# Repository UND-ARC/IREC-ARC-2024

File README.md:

# IREC-Launch-Vehicle-2024
UND ARC Launch Vehicle for Spaceport America Cup 2024 

### Hardware
Link to Hardware List [WIP]
### Software
- Solidworks Student Edition 2022
- OpenRocket
- GIT
- GIT LFS (Large File Support)
- GitHub Desktop
## Getting Started
### Installing and Setting Up the Repository
1) Create a GitHub Account
2) Download and install Git [LINK](https://git-scm.com/downloads)
3) Download and install Git LFS [LINK](https://git-lfs.github.com/)
4) Download and install GitHub Desktop [LINK](https://desktop.github.com/)
5) Sign into GitHub Desktop with GitHub Account
6) Create a local copy of the Repository opeing 'File -> Clone repository -> URL'
7) Enter: [https://github.com/UND-ARC/RocketModels-2023.git](https://github.com/UND-ARC/RocketModels-2023.git)
8) Set your local path to 'C:/Projects/RocketModels-2023'. Note, you may need to create manually the Projects folder (do not create the 'RocketModels-2023' folder)
9) Open file explorer and navigate to 'C:/Projects/RocketModels-2023'
10) Right click in the folder and select 'Git Bash Here'
11) Enter the command `git lfs install`. This will enable the large file support.
12) Message Neko'z in discord to get added to the members list for write access
### When editing files
Since files are stored as binary (unreadable to humans) it is important that no two file have a merge conflict. This can be done by "locking" a file when we edit it which prevents others from making changes to it at the same time.

To Lock a file, right click in the folder the file is in and select "Git bash here". Then enter the command:
`git lfs lock FILENAME.Ext`
To Unlock a file use the command:
`git lfs unlock FILENAME.Ext`
The command `ls` will list all the files in the current folder if you don't know the extension. To see all the files that are currently locked, `git lfs locks` will list who has locked what.

To sumarize the editing process:
1) Pull the current files from the server
2) Lock the file using `git lfs lock FILENAME`
3) Edit the file
4) Add changes to the commits `git add FILENAME` or `git add --all`
5) Commit the edits with a description using GitHub Desktop with `git commit -m 'MESSAGE GOES HERE'`
6) `git pull` and `git push` the new commits to the server (Contact Neko'z or Galbatorix if you get an error!)
7) Unlock the file using `git lfs unlock FILENAME`

## Version History
### Alpha 1.0
Yay!
## Authors
- [Neko'z](mailto:zachariah.palmer@und.edu)
- [Galbatorix](mailto:mason.motschke@und.edu)
- [JRLemker](mailto:joseph.lemker@und.edu)
## License
[MIT](LICENSE)
## Acknologements
WIP

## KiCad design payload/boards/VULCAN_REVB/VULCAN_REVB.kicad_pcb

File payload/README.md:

# Spaceport America Cup Payload

Nose Cone Heat Transfer and Live Transmitting of Sensor Data and Video

## Payload Description

N/A

## Getting Started

### Hardware

N/A

### Software
- C++ w/ Arduino IDE
- Python
- PCB designed in KiCad 7.0

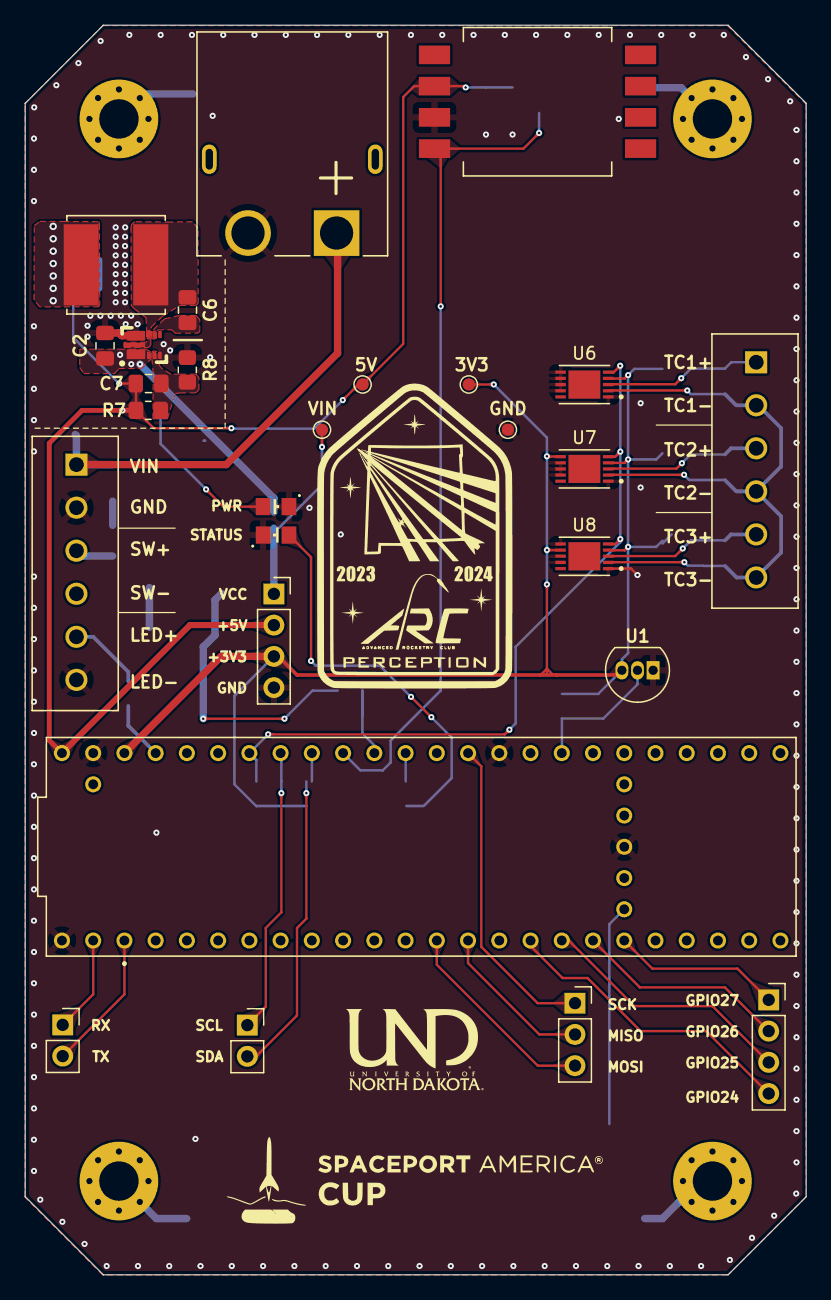
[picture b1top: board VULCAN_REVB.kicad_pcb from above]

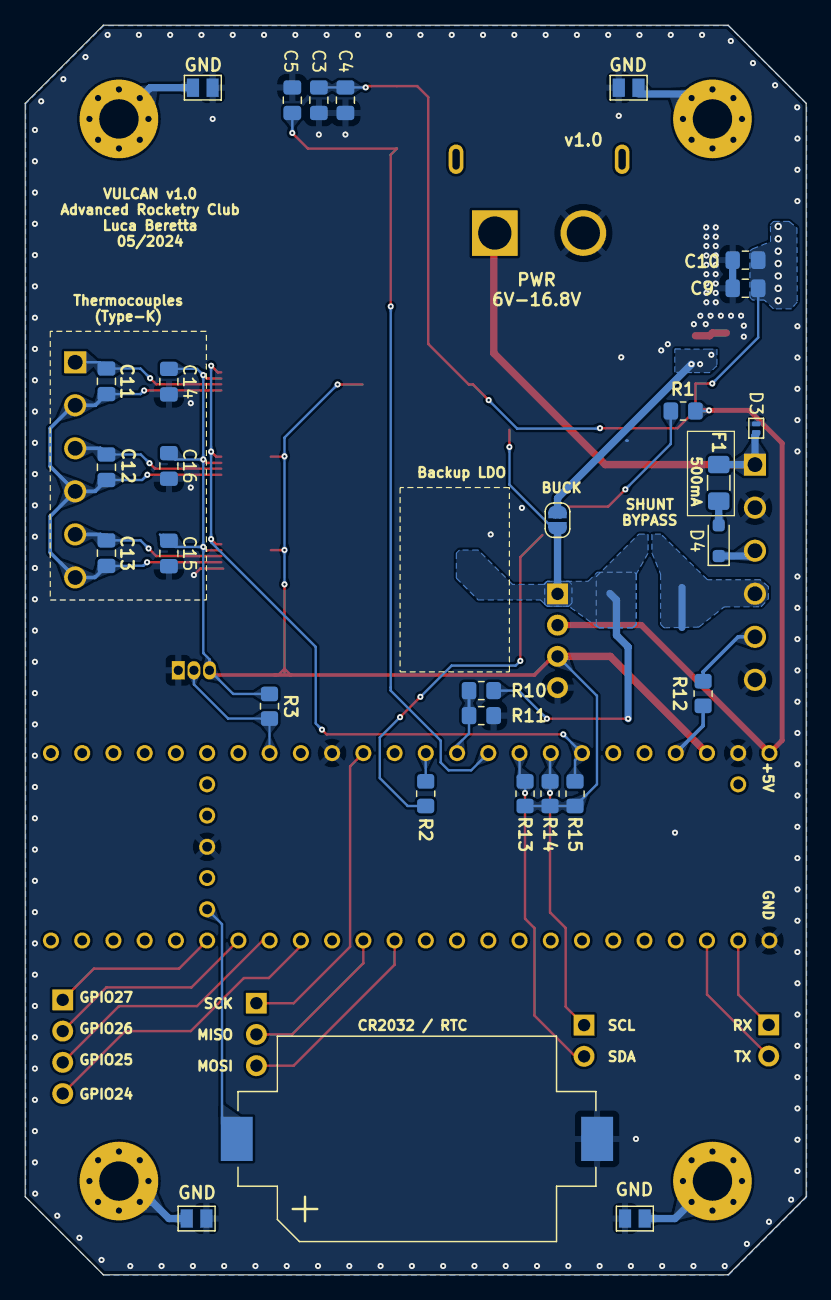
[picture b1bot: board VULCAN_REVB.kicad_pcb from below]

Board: 2 copper layers, 63.5 x 101.6 mm, 61 parts (29 on the bottom side), 40 nets.

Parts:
BT1: Battery_Cell; BatteryHolder_Keystone_1060_1x2032
C2: 10uF; C_0805_2012Metric_Pad1.18x1.45mm_HandSolder
C3, C11, C12, C13: 0.01uF; C_0805_2012Metric_Pad1.18x1.45mm_HandSolder
C4: 1.0uF; C_0805_2012Metric_Pad1.18x1.45mm_HandSolder
C5: 470pF; C_0805_2012Metric_Pad1.18x1.45mm_HandSolder
C6, C14, C15, C16: 0.1uF; C_0805_2012Metric_Pad1.18x1.45mm_HandSolder
C7: 47pF; C_0805_2012Metric_Pad1.18x1.45mm_HandSolder
C9, C10: 22uF; C_0805_2012Metric_Pad1.18x1.45mm_HandSolder
D1: CMD17-21VRD/TR8; OSRAM_0805
D2: CMD17-21VGD/TR8; OSRAM_0805
D3: SPHV12-01ETG-C; D_SOD-882_DFN1006-2_TVS
D4: BAT165AX; D_SOD-323_HandSoldering
F1: 500mA; Fuse_1206_3216Metric_Pad1.42x1.75mm_HandSolder
G1: LOGO
H1, H2, H3, H4: MountingHole_Pad; MountingHole_3.2mm_M3_Pad_Via
J1: XT60PW-M; AMASS_XT60PW-M
J2: POWER; PinSocket_1x04_P2.54mm_Vertical
J3: I2C; PinSocket_1x02_P2.54mm_Vertical
J4: Serial; PinSocket_1x02_P2.54mm_Vertical
J5: SPI; PinSocket_1x03_P2.54mm_Vertical
J6: GPIO; PinSocket_1x04_P2.54mm_Vertical
J7, J8: Screw_Terminal_01x06; TERMBLOCK_OSTTE060104
JP1: Jumper_2_Open; SolderJumper-2_P1.3mm_Open_RoundedPad1.0x1.5mm
JP3, JP4, JP5, JP6: Jumper_2_Open; SolderJumper
L1: 6.8uH; IND_SRN8040TA-6R8M
R1: 150; R_0805_2012Metric_Pad1.20x1.40mm_HandSolder
R2: 62; R_0805_2012Metric_Pad1.20x1.40mm_HandSolder
R3, R13, R14, R15: 4.7k; R_0805_2012Metric_Pad1.20x1.40mm_HandSolder
R7: 220k; R_0805_2012Metric_Pad1.20x1.40mm_HandSolder
R8: 41.2k; R_0805_2012Metric_Pad1.20x1.40mm_HandSolder
R10: 300k; R_0805_2012Metric_Pad1.20x1.40mm_HandSolder
R11: 100k; R_0805_2012Metric_Pad1.20x1.40mm_HandSolder
R12: R; R_0805_2012Metric_Pad1.20x1.40mm_HandSolder
TP1: GND; TestPoint_Pad_D1.0mm
TP2: +5V; TestPoint_Pad_D1.0mm
TP3: +3V3; TestPoint_Pad_D1.0mm
TP4: VIN; TestPoint_Pad_D1.0mm
U1: DS18B20+; TO-92_Inline
U3: MPXV7002DP; XDCR_MPXV7002DP
U4: AP63357QZV-7; AP63356 (V-DFN3020-13)
U5: Teensy 4.1; MODULE_DEV-16771
U6, U7, U8: MAX31850KATB+T; SON50P300X400X80-11N

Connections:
+3V3: C14.1, C15.1, C16.1, J2.3, R3.1, R13.1, R14.1, R15.2, TP3.1, U1.3 (V_{DD}), U5.3.3V_2 (3.3V__1), U6.4 (VDD), U7.4 (VDD), U7.6 (AD0), U8.4 (VDD), U8.7 (AD1)
/+5V: C3.1, C4.1, C7.1, C9.1, C10.1, J2.2, L1.2, R1.1, R7.1, TP2.1, U3.2 (VS), U5.VIN
/BOARD_TEMP: R3.2, U1.2 (DQ), U5.40 (A16)
/GPIO24: J6.4, U5.24 (A10)
/GPIO25: J6.3, U5.25 (A11)
/GPIO26: J6.2, U5.26 (A12)
/GPIO27: J6.1, U5.27 (A13)
/I2C_SCL: J3.1, R14.2, U5.19 (A5)
/I2C_SDA: J3.2, R13.2, U5.18 (A4)
/LED_EXT: R12.1, U5.23 (A9)
/LED_GRN: R2.2, U5.15 (A1)
/PITOT: C5.1, U3.4 (VOUT), U5.17 (A3)
/RX: J4.1, U5.0 (RX1)
/SPI_MISO: J5.2, U5.12 (MISO)
/SPI_MOSI: J5.3, U5.11 (MOSI)
/SPI_SCK: J5.1, U5.13 (SCK)
/T1: C11.1, J8.1, U6.3 (T+)
/T2: C12.1, J8.3, U7.3 (T+)
/T3: C13.1, J8.5, U8.3 (T+)
/T-: C11.2, C12.2, C13.2, J8.2, J8.4, J8.6, U6.2 (T-), U7.2 (T-), U8.2 (T-)
/TC_DATA: R15.1, U5.20 (A6), U6.5 (DQ), U7.5 (DQ), U8.5 (DQ)
/TX: J4.2, U5.1 (TX1)
/VBAT: D3.2 (A2), F1.1, J1.1 (+), J7.1
/VBAT_COIN: BT1.1 (+), U5.VBAT
/VBAT_RP: D4.1 (K), J7.3
/VCC: J2.1, JP1.1 (A), R10.1, TP4.1
/VCC_SENSE: R10.2, R11.1, U5.16 (A2)
GND: BT1.2 (-), C2.2, C3.2, C4.2, C5.2, C9.2, C10.2, C14.2, C15.2, C16.2, D1.C, D2.C, D3.1 (A1), J1.2 (-), J2.4, J7.2, J7.6, JP3.2 (B), JP4.2 (B), JP5.2 (B), JP6.2 (B), R8.2, R11.2, TP1.1, U1.1 (GND), U3.3 (GND), U4.4 (COMP), U4.8 (GND), U5.GND1 (GND), U5.GND2 (GND__1), U5.GND3 (GND__2), U5.GND4 (GND__3), U6.1 (GND), U6.6 (AD0), U6.7 (AD1), U6.8 (AD2), U6.9 (AD3), U7.1 (GND), U7.7 (AD1), U7.8 (AD2), U7.9 (AD3), U8.1 (GND), U8.6 (AD0), U8.8 (AD2), U8.9 (AD3)
unnamed: D1.A, R1.2
unnamed: D2.A, R2.1
unnamed: D4.2 (A), F1.2
unnamed: J7.5, R12.2
unnamed: C2.1, JP1.2 (B), U4.1 (VIN), U4.2 (EN)
unnamed: H1.1, JP3.1 (A)
unnamed: H2.1, JP4.1 (A)
unnamed: H3.1, JP5.1 (A)
unnamed: H4.1, JP6.1 (A)
unnamed: C6.1, U4.6 (BST)
unnamed: C7.2, R7.2, R8.1, U4.3 (FB)
unnamed: C6.2, L1.1, U4.9 (SW)

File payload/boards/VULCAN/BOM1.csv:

Reference,Value,DKPN,Distributor,MPN,Qty,New Qty
J3,I2C,WM23663-ND,DigiKey,901471102,1,2
J4,Serial,WM23663-ND,DigiKey,901471102,1,2
J5,SPI,WM14830-ND,DigiKey,901471103,1,2
J2,POWER,WM14831-ND,DigiKey,901471104,1,2
J6,GPIO,WM14831-ND,DigiKey,901471104,1,2
BT1,Battery_Cell,36-1060-ND,DigiKey,1060,1,2
F1,500mA,F3733CT-ND,DigiKey,  1206L050/15YR,1,5
U2,AZ1117IH-5.0TRG1,AZ1117IH-5.0TRG1DICT-ND,DigiKey,  AZ1117IH-5.0TRG1,1,5
C4,1.0uF,311-3498-1-ND,DigiKey,  CC0805JKX7R9BB105,1,5
IC1,LT1001CS8#PBF,505-LT1001CS8#PBF-ND,DigiKey,  LT1001CS8#PBF,1,3
U3,MPXV7002DP,MPXV7002DP-ND,DigiKey,  MPXV7002DP,1,2
"J7,J8",Screw_Terminal_01x06,ED2744-ND,DigiKey,  OSTTE060104,2,4
HS1,Heatsink,,Sparkfun, PRT-18704,1,2
L1,6.8uH,SRN8040TA-6R8MCT-ND,DigiKey, SRN8040TA-6R8M,1,2
R12,R,,-,-,1,
U4,AP63357QZV-7,31-AP63357QZV-7CT-ND,DigiKey,AP63357QZV-7,1,5
D4,BAT165AX,1727-2752-1-ND,DigiKey,BAT165AX,1,5
C7,47pF,311-1107-1-ND,DigiKey,CC0805JRNPO9BN470,1,5
C5,470pF,311-1119-1-ND,DigiKey,CC0805JRNPO9BN471,1,5
"C3,C11,C12,C13",0.01uF,311-1857-1-ND,DigiKey,CC0805JRX7R9BB103,4,10
"C6,C14,C15,C16",0.1uF,311-1858-1-ND,DigiKey,CC0805JRX7R9BB104,4,10
"C2,C8",10uF,311-1869-1-ND,DigiKey,CC0805KKX5R8BB106,2,10
"C1,C9,C10",22uF,311-1903-1-ND,DigiKey,CC0805MKX5R8BB226,3,10
D2,CMD17-21VGD/TR8,L62505CT-ND,DigiKey,CMD17-21VGD/TR8,1,5
D1,CMD17-21VRD/TR8,L62501CT-ND,DigiKey,CMD17-21VRD/TR8,1,5
U1,DS18B20+,DS18B20+-ND,DigiKey,DS18B20+,1,5
"U6,U7,U8",MAX31850KATB+T,MAX31850KATB+TCT-ND,DigiKey,MAX31850KATB+T,3,10
R2,62,311-62.0CRCT-ND,DigiKey,RC0805FR-0762RL,1,10
R1,150,311-150CRCT-ND,DigiKey,RC0805FR-07150RL,1,10
"R4,R5",1K,311-1.00KCRCT-ND,DigiKey,RC0805FR-071KL,2,10
R11,100k,311-100KCRCT-ND,DigiKey,RC0805FR-07100KL,1,10
R8,41.2k,311-41.2KCRCT-ND,DigiKey,RC0805FR-0741K2L,1,10
"R3,R13,R14,R15",4.7k,311-4.70KCRCT-ND,DigiKey,RC0805FR-074K7L,4,15
"R6,R9",5.1K,311-5.10KCRCT-ND,DigiKey,RC0805FR-075K1L,2,10
R7,220k,311-220KARCT-ND,DigiKey,RC0805JR-07220KL,1,10
R10,300k,311-300KARCT-ND,DigiKey,RC0805JR-07300KL,1,10
D3,SPHV12-01ETG-C,F6505CT-ND,DigiKey,SPHV12-01ETG-C,1,10
R_Shunt1,0.05,541-3281-1-ND,DigiKey,WSHP2818R0500FEA,1,10
J1,XT60PW-M,,TME,XT60PW-M,1,

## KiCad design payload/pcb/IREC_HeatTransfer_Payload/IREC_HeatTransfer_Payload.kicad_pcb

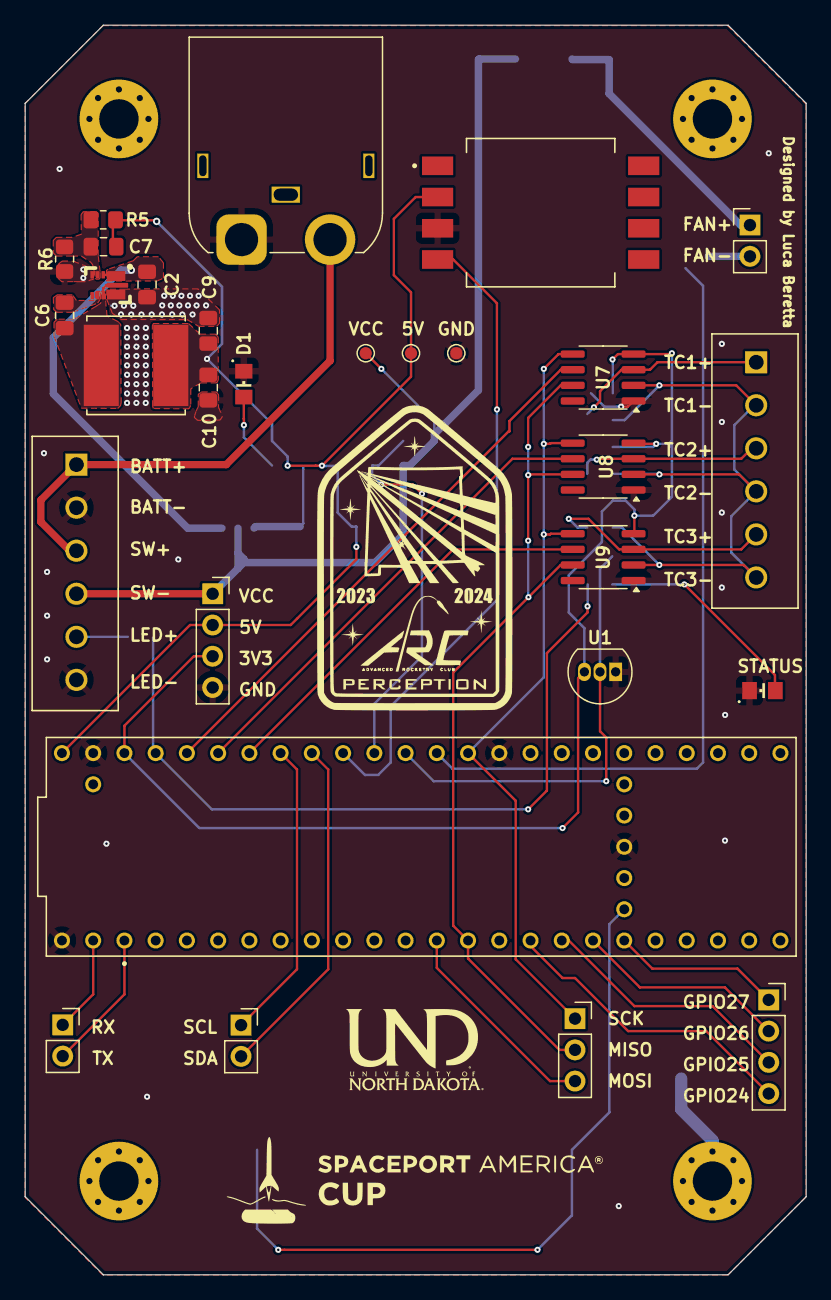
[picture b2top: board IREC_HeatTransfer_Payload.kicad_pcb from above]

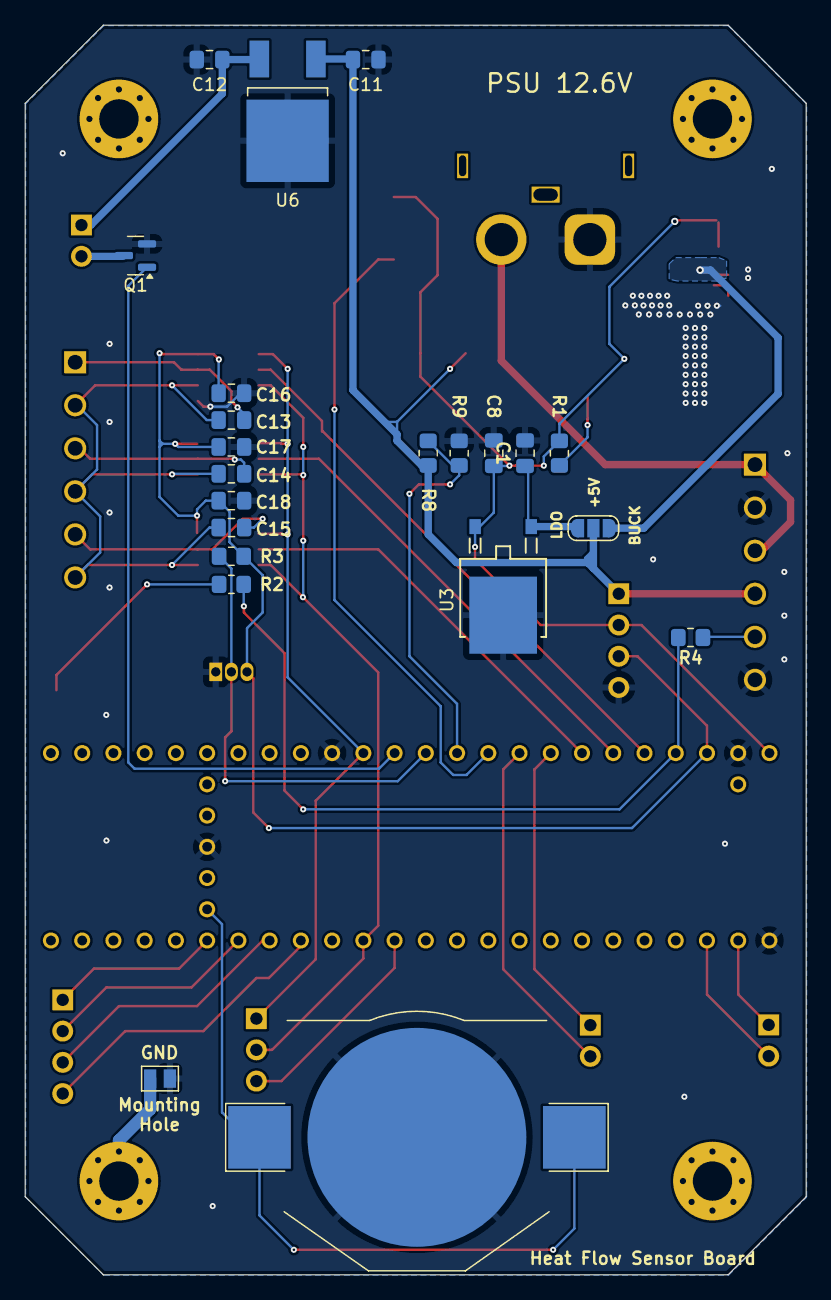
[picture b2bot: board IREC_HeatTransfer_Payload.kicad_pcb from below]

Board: 2 copper layers, 63.5 x 101.6 mm, 56 parts (22 on the bottom side), 40 nets.

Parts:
BT1: Battery_Cell; BatteryHolder_Keystone_3002_1x2032
C1, C11: 0.33uF; C_0805_2012Metric_Pad1.18x1.45mm_HandSolder
C2: 10uF; C_0805_2012Metric_Pad1.18x1.45mm_HandSolder
C6: 0.1u; C_0805_2012Metric_Pad1.18x1.45mm_HandSolder
C7: 47pF; C_0805_2012Metric_Pad1.18x1.45mm_HandSolder
C8, C12, C16, C17, C18: 0.1uF; C_0805_2012Metric_Pad1.18x1.45mm_HandSolder
C9, C10: 22uF; C_0805_2012Metric_Pad1.18x1.45mm_HandSolder
C13, C14, C15: 100n; C_0805_2012Metric_Pad1.18x1.45mm_HandSolder
D1: OSRAM_LSR976-NR-1; OSRAM_0805
D2: OSRAM_LGR971-KN-1; OSRAM_0805
G1: LOGO
H1, H2, H3, H4: MountingHole_Pad; MountingHole_3.2mm_M3_Pad_Via
J1: POWER; PinSocket_1x04_P2.54mm_Vertical
J2: I2C; PinSocket_1x02_P2.54mm_Vertical
J3: Serial; PinSocket_1x02_P2.54mm_Vertical
J4: SPI; PinSocket_1x03_P2.54mm_Vertical
J5: GPIO; PinSocket_1x04_P2.54mm_Vertical
J6: XT60PW-M; AMASS_XT60IPW-M_1x03_P7.20mm_Horizontal
J7, J8: Screw_Terminal_01x06; TERMBLOCK_OSTTE060104
J9: FAN; PinHeader_1x02_P2.54mm_Vertical
JP1: Jumper_3_Open; SolderJumper-3_P1.3mm_Open_RoundedPad1.0x1.5mm
JP2: Jumper_2_Open; SolderJumper
L1: 6.8uH; IND_SRN8040TA-6R8M
Q1: 2N7002K; SOT-23
R1, R2, R4: R; R_0805_2012Metric_Pad1.20x1.40mm_HandSolder
R3: 4.7k; R_0805_2012Metric_Pad1.20x1.40mm_HandSolder
R5: 220k; R_0805_2012Metric_Pad1.20x1.40mm_HandSolder
R6: 41.2k; R_0805_2012Metric_Pad1.20x1.40mm_HandSolder
R8: 200k; R_0805_2012Metric_Pad1.20x1.40mm_HandSolder
R9: 100k; R_0805_2012Metric_Pad1.20x1.40mm_HandSolder
TP1: VIN; TestPoint_Pad_D1.0mm
TP2: GND; TestPoint_Pad_D1.0mm
TP3: +5V; TestPoint_Pad_D1.0mm
U1: DS18B20; TO-92_Inline
U2: MPXV7002DP; XDCR_MPXV7002DP
U3: NJM7805SDL1-TE1; TO-252-3-L1_NMD
U4: AP63357; AP63356 (V-DFN3020-13)
U5: DEV-16771; MODULE_DEV-16771
U6: L78M12CDT-TR; VREG_L78M12CDT-TR
U7, U8, U9: MAX31855KASA; SOIC-8_3.9x4.9mm_P1.27mm

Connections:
5V_BUCK: C2.1, JP1.3 (B), U4.1 (VIN), U4.2 (EN)
5V_LDO: C1.1, JP1.1 (A), U3.1 (VIN)
+3V3: C16.1, C17.1, C18.1, J1.3, R3.1, U1.3 (V_{DD}), U5.3.3V_2 (3.3V__1), U7.4 (V_CC), U8.4 (V_CC), U9.4 (V_CC)
+5V: C7.1, C8.1, C9.1, C10.1, J1.2, L1.2, R1.1, R5.1, TP3.1, U2.2 (VS), U3.3 (VOUT), U5.VIN
/+12V: C12.1, J9.1, U6.3 (OUT)
/+BATT: J6.2 (+), J7.1, J7.3
/+VCC: C11.1, J1.1, J7.4, JP1.2 (C), R8.1, TP1.1, U6.1 (IN)
/DS18_TEMP: R3.2, U1.2 (DQ), U5.15 (A1)
/FAN: Q1.1 (G), U5.14 (A0)
/GPIO24: J5.4, U5.24 (A10)
/GPIO25: J5.3, U5.25 (A11)
/GPIO26: J5.2, U5.26 (A12)
/GPIO27: J5.1, U5.27 (A13)
/I2C_SCL: J2.1, U5.19 (A5)
/I2C_SDA: J2.2, U5.18 (A4)
/LED_GREEN: R2.2, R4.2, U5.23 (A9)
/PITOT: U2.4 (VOUT), U5.17 (A3)
/RX: J3.1, U5.0 (RX1)
/SPI_MISO: J4.2, U5.12 (MISO), U7.7 (SO), U8.7 (SO), U9.7 (SO)
/SPI_MOSI: J4.3, U5.11 (MOSI)
/SPI_SCK: J4.1, U5.13 (SCK), U7.5 (SCK), U8.5 (SCK), U9.5 (SCK)
/T1: C13.1, J8.1, U7.3 (T+)
/T1_CS: U5.22 (A8), U7.6 (~CS)
/T2: C14.1, J8.3, U8.3 (T+)
/T2_CS: U5.21 (A7), U8.6 (~CS)
/T3: C15.1, J8.5, U9.3 (T+)
/T3_CS: U5.20 (A6), U9.6 (~CS)
/T-: C13.2, C14.2, C15.2, J8.2, J8.4, J8.6, U7.2 (T-), U8.2 (T-), U9.2 (T-)
/TX: J3.2, U5.1 (TX1)
/VBAT_COIN: BT1.1 (+), U5.VBAT
/VBAT_SENSE: R8.2, R9.1, U5.16 (A2)
GND: BT1.2 (-), C1.2, C2.2, C8.2, C9.2, C10.2, C11.2, C12.2, C16.2, C17.2, C18.2, D1.C, D2.C, J1.4, J6.1 (-), J7.2, J7.6, JP2.2 (B), Q1.2 (S), R6.2, R9.2, TP2.1, U1.1 (GND), U2.3 (GND), U3.2 (GND), U4.4 (COMP), U4.8 (GND), U5.GND1 (GND), U5.GND2 (GND__1), U5.GND3 (GND__2), U5.GND4 (GND__3), U6.2 (GND), U7.1 (GND), U8.1 (GND), U9.1 (GND)
unnamed: D1.A, R1.2
unnamed: D2.A, R2.1
unnamed: J7.5, R4.1
unnamed: J9.2, Q1.3 (D)
unnamed: H4.1, JP2.1 (A)
unnamed: C6.1, U4.6 (BST)
unnamed: C7.2, R5.2, R6.1, U4.3 (FB)
unnamed: C6.2, L1.1, U4.9 (SW)

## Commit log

2023-10-19 test
2023-10-19 second test
2023-10-19 hope this works
2023-10-19 this better work
2023-10-19 this is taking forever
2023-10-19 final test
2023-10-20 IREC Rocket Design and simulations
2023-11-15 Small Scale IREC
2023-12-15 Added fin flutter analysis. Still need to double check
2023-12-15 Updated fin flutter analysis
2023-12-15 Updated fin flutter velocity
2024-01-18 Fin Flutter Analysis
2024-02-11 Updated OpenRocket and Flight Simulations
2024-02-11 Subscale Flight Sim
2024-02-14 New fin flutter analysis from new source
2024-02-14 Fin flutter source added
2024-02-16 New Flight Sims
2024-02-20 New Subscale Design
2024-04-17 Create Payload
2024-04-17 Delete Payload
    whoops
2024-04-19 New PCBs!
2024-04-19 reorganization and readme
2024-04-20 moreChanges
2024-04-21 updates to pcb
2024-04-21 moreupdates
2024-04-22 updates
    continued buck layout
2024-04-24 added pitot
2024-04-24 began routing
2024-04-25 GPIOs renamed
2024-04-26 rework
2024-05-02 added router file
2024-05-02 updates
    1-wire sensor
2024-05-06 rework
    boost converter stuff
2024-05-06 reverted back to bucks
    since we need weight in the form of batteries
2024-05-07 Updated openrocket
2024-05-07 openrocket files will update further later
2024-05-07 Boat Tail Step File
2024-05-08 added ESD to TCs
2024-05-10 updated BOM
    distributor and manufacturer part number
2024-05-10 updated BOM
2024-05-18 added graphics
2024-06-08 misc updates
2024-06-10 code
2024-06-13 new code
2024-06-18 Add files via upload
    V3 with no boattail
2024-07-06 Flight Data
2024-07-06 Nosecone Flight Data
